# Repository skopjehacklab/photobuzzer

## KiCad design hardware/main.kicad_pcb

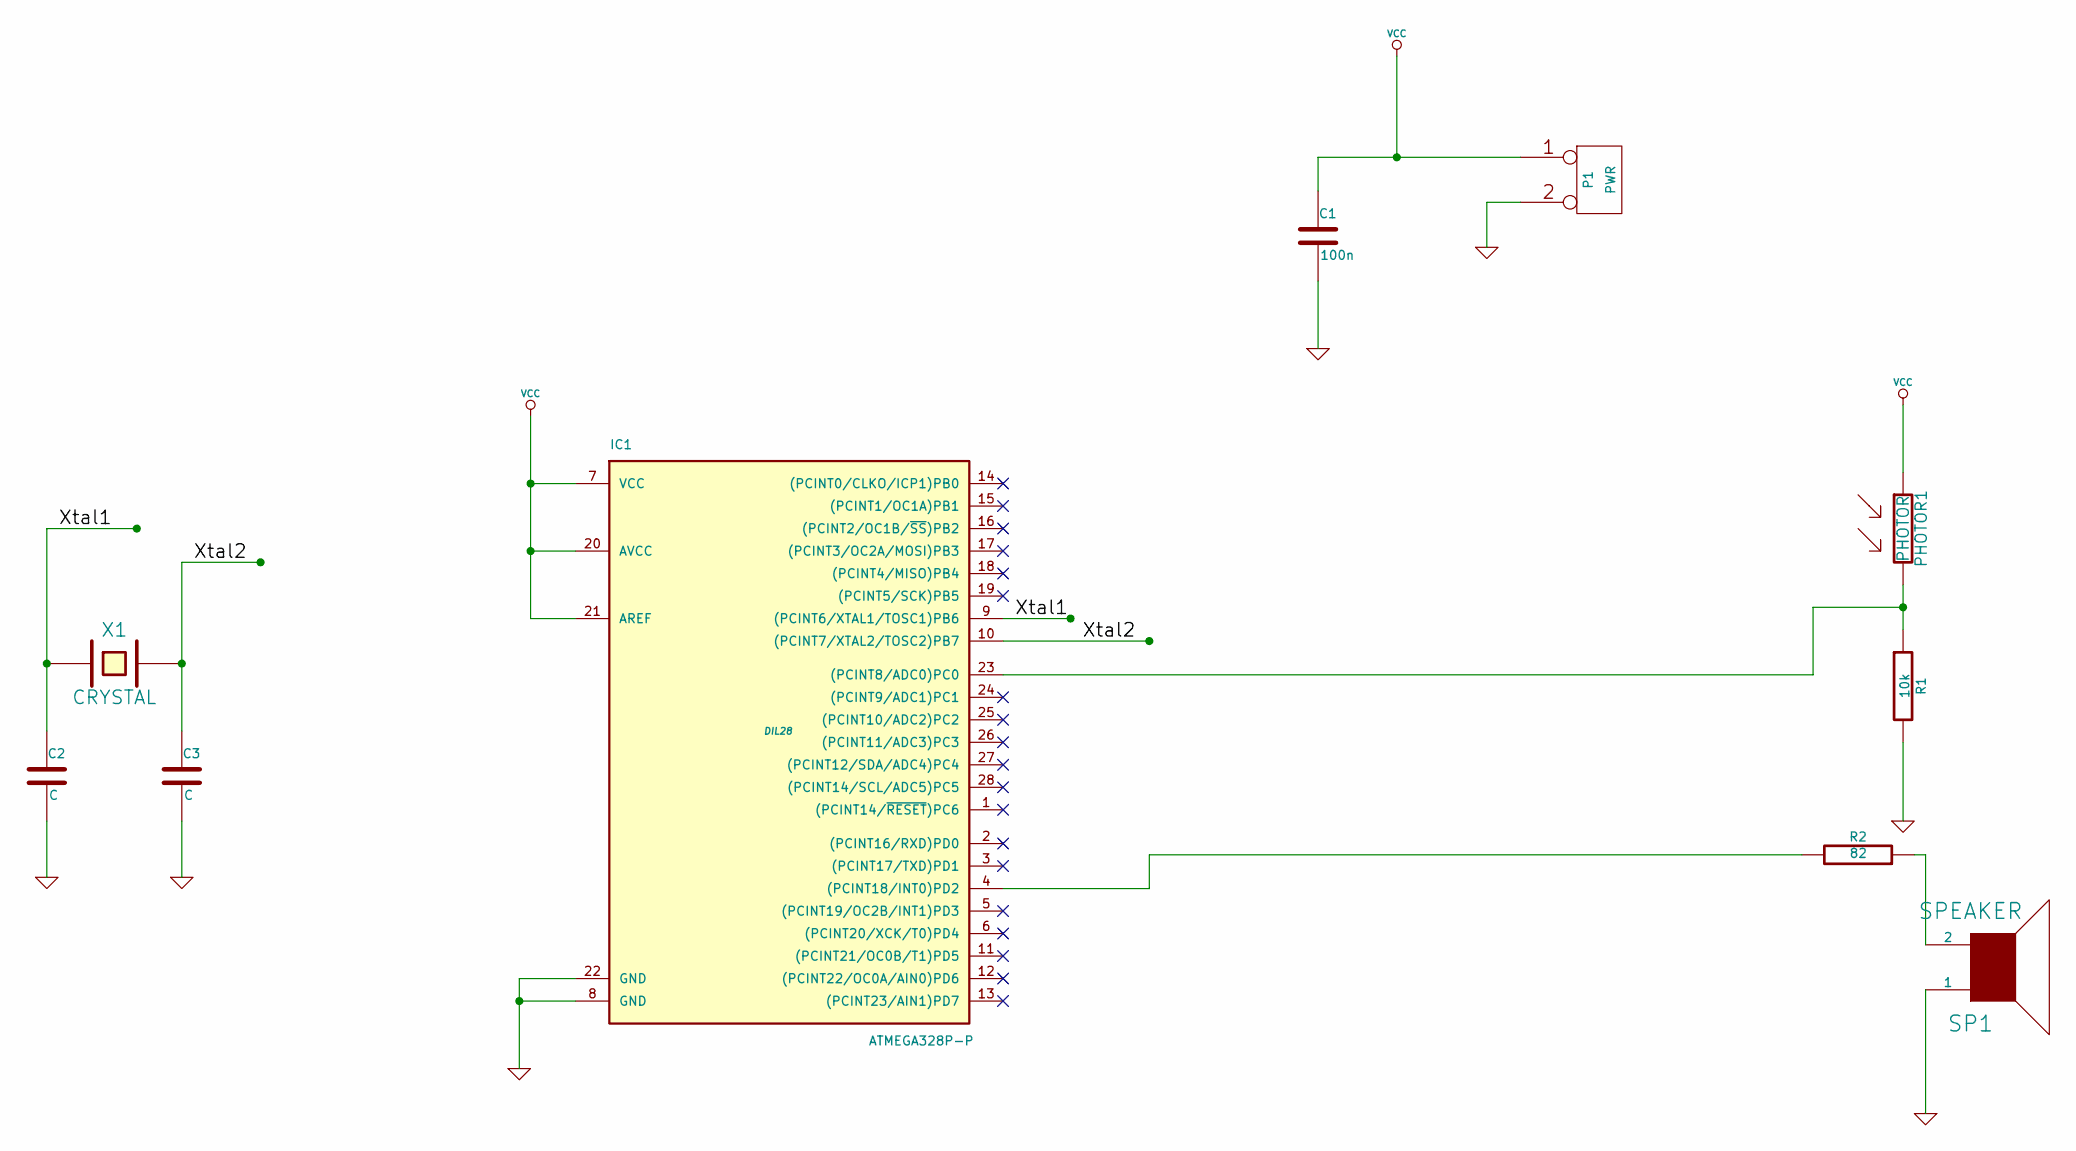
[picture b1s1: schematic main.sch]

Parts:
C1: 100n
C2, C3: C
IC1: ATMEGA328P-P; DIL28
P1: PWR
PHOTOR1: PHOTOR
R1: 10k
R2: 82
SP1: SPEAKER
X1: CRYSTAL

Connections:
/Xtal1: C2.1, IC1.9 ((PCINT6/XTAL1/TOSC1)PB6), X1.1
/Xtal2: C3.1, IC1.10 ((PCINT7/XTAL2/TOSC2)PB7), X1.2
GND: C1.2, C2.2, C3.2, IC1.8 (GND), IC1.22 (GND), P1.2 (PM), R1.2, SP1.1
unnamed: R2.1, SP1.2
unnamed: IC1.4 ((PCINT18/INT0)PD2), R2.2
unnamed: IC1.23 ((PCINT8/ADC0)PC0), PHOTOR1.2, R1.1
VCC: C1.1, IC1.7 (VCC), IC1.20 (AVCC), IC1.21 (AREF), P1.1, PHOTOR1.1

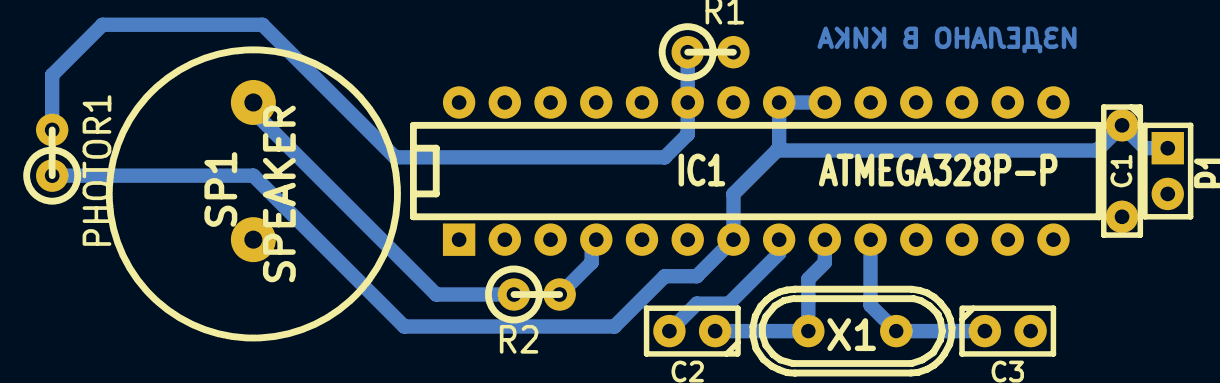
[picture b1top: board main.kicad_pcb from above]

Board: 2 copper layers, 10 parts (0 on the bottom side), 7 nets.

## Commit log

2013-12-14 Arduino code that works.
2013-12-14 Added the related hardware files
2013-12-28 Added some info and made a PDF version of the schematic
2013-12-28 Added the location of the components and changed the location of the references on the PCB
